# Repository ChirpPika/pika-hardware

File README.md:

# pika-hardware
Hardware design for all Pika models

KiCAD 10

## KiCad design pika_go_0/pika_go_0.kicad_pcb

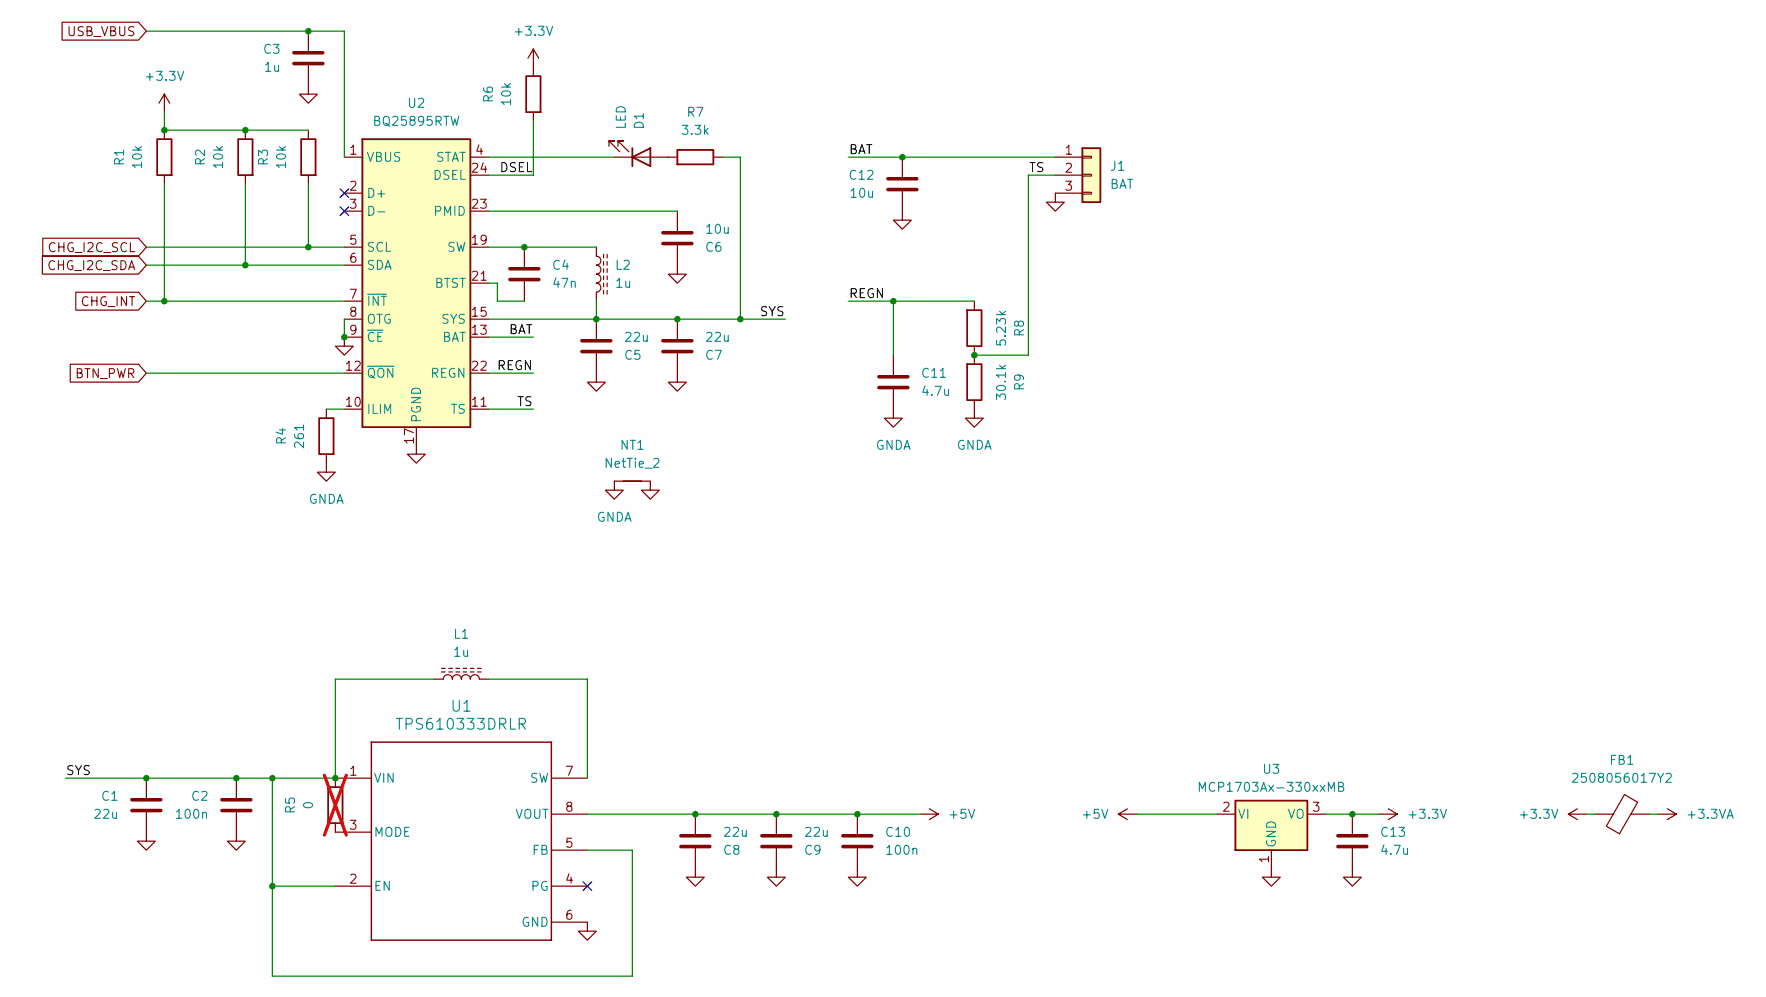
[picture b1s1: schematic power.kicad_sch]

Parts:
C1, C5, C7, C8, C9: 22u; C_0805_2012Metric_Pad1.18x1.45mm_HandSolder
C2, C10: 100n; C_0603_1608Metric_Pad1.08x0.95mm_HandSolder
C3: 1u; C_0603_1608Metric_Pad1.08x0.95mm_HandSolder
C4: 47n; C_0603_1608Metric_Pad1.08x0.95mm_HandSolder
C6, C12: 10u; C_0603_1608Metric_Pad1.08x0.95mm_HandSolder
C11, C13: 4.7u; C_0603_1608Metric_Pad1.08x0.95mm_HandSolder
D1: LED; LED_0603_1608Metric_Pad1.05x0.95mm_HandSolder
FB1: 2508056017Y2; L_0805_2012Metric_Pad1.05x1.20mm_HandSolder
J1: BAT; JST_PH_S3B-PH-K_1x03_P2.00mm_Horizontal
L1, L2: 1u; L_ABRACON_AMELH4018S
NT1: NetTie_2; NetTie-2_SMD_Pad0.5mm
R1, R2, R3, R6: 10k; R_0603_1608Metric_Pad0.98x0.95mm_HandSolder
R4: 261; R_0603_1608Metric_Pad0.98x0.95mm_HandSolder; Tolerance 1%
R5: 0; R_0603_1608Metric_Pad0.98x0.95mm_HandSolder; not fitted
R7: 3.3k; R_0603_1608Metric_Pad0.98x0.95mm_HandSolder
R8: 5.23k; R_0603_1608Metric_Pad0.98x0.95mm_HandSolder; Tolerance 1%
R9: 30.1k; R_0603_1608Metric_Pad0.98x0.95mm_HandSolder; Tolerance 1%
U1: TPS610333DRLR; SOT-583-8
U2: BQ25895RTW; Texas_RTW_WQFN-24-1EP_4x4mm_P0.5mm_EP2.7x2.7mm_ThermalVias
U3: MCP1703Ax-330xxMB; SOT-89-3

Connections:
+3.3V: C13.1, FB1.1, R1.1, R2.1, R3.1, R6.1, U3.3 (VO); also elsewhere on the board
+3.3VA: FB1.2; also elsewhere on the board
+5V: C8.2, C9.2, C10.1, U1.8 (VOUT), U3.2 (VI); also elsewhere on the board
/Power/BAT: C12.1, J1.1, U2.13 (BAT), U2.14 (BAT)
/Power/DSEL: R6.2, U2.24 (DSEL)
/Power/REGN: C11.1, R8.2, U2.22 (REGN)
/Power/SYS: C1.1, C2.1, C5.2, C7.2, L1.1, L2.2, R5.1, R7.1, U1.1 (VIN), U1.2 (EN), U1.5 (FB), U2.15 (SYS), U2.16 (SYS)
/Power/TS: J1.2, R8.1, R9.2, U2.11 (TS)
BTN_PWR: U2.12 (~QON); also elsewhere on the board
CHG_I2C_SCL: R3.2, U2.5 (SCL); also elsewhere on the board
CHG_I2C_SDA: R2.2, U2.6 (SDA); also elsewhere on the board
CHG_INT: R1.2, U2.7 (~INT); also elsewhere on the board
GND: C1.2, C2.2, C3.2, C5.1, C6.1, C7.1, C8.1, C9.1, C10.2, C12.2, C13.2, J1.3, NT1.2, U1.6 (GND), U2.8 (OTG), U2.9 (~CE), U2.17 (PGND), U2.18 (PGND), U2.25 (PGND), U3.1 (GND); also elsewhere on the board
GNDA: C11.2, NT1.1, R4.2, R9.1
unnamed: C4.1, L2.1, U2.19 (SW), U2.20 (SW)
unnamed: D1.2 (A), R7.2
unnamed: D1.1 (K), U2.4 (STAT)
unnamed: R5.2, U1.3 (MODE)
unnamed: L1.2, U1.7 (SW)
unnamed: C4.2, U2.21 (BTST)
unnamed: R4.1, U2.10 (ILIM)
unnamed: C6.2, U2.23 (PMID)
USB_VBUS: C3.1, U2.1 (VBUS); also elsewhere on the board

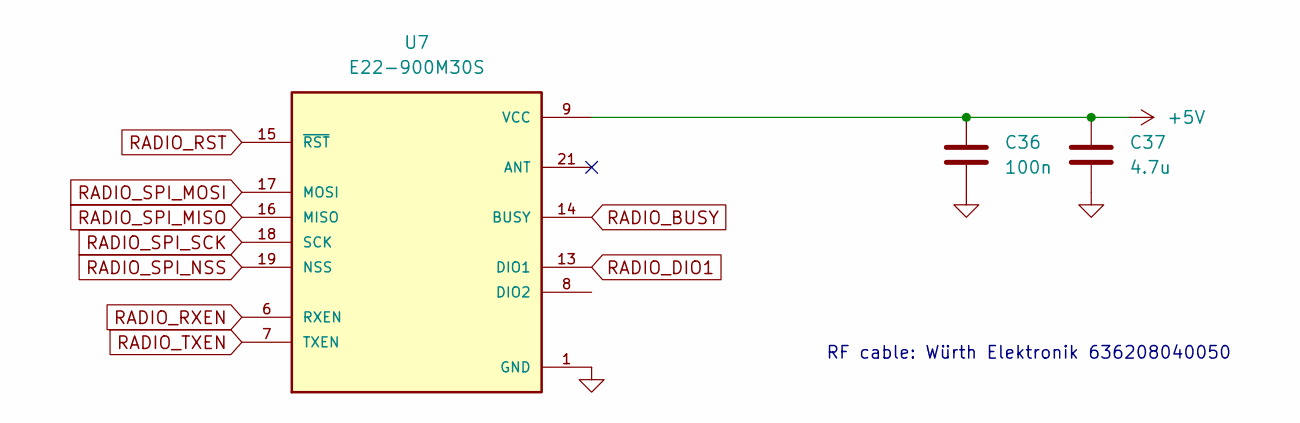
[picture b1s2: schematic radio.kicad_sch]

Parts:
C36: 100n; C_0603_1608Metric_Pad1.08x0.95mm_HandSolder
C37: 4.7u; C_0603_1608Metric_Pad1.08x0.95mm_HandSolder
U7: E22-900M30S; XCVR_E22-900M30S; PARTREV 1.2

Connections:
+5V: C36.1, C37.1, U7.9 (VCC), U7.10 (VCC); also elsewhere on the board
GND: C36.2, C37.2, U7.1 (GND), U7.2 (GND), U7.3 (GND), U7.4 (GND), U7.5 (GND), U7.11 (GND), U7.12 (GND), U7.20 (GND), U7.22 (GND); also elsewhere on the board
RADIO_BUSY: U7.14 (BUSY); also elsewhere on the board
RADIO_DIO1: U7.13 (DIO1); also elsewhere on the board
RADIO_RST: U7.15 (~RST); also elsewhere on the board
RADIO_RXEN: U7.6 (RXEN); also elsewhere on the board
RADIO_SPI_MISO: U7.16 (MISO); also elsewhere on the board
RADIO_SPI_MOSI: U7.17 (MOSI); also elsewhere on the board
RADIO_SPI_NSS: U7.19 (NSS); also elsewhere on the board
RADIO_SPI_SCK: U7.18 (SCK); also elsewhere on the board
RADIO_TXEN: U7.7 (TXEN); also elsewhere on the board

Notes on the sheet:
RF cable: Würth Elektronik 636208040050

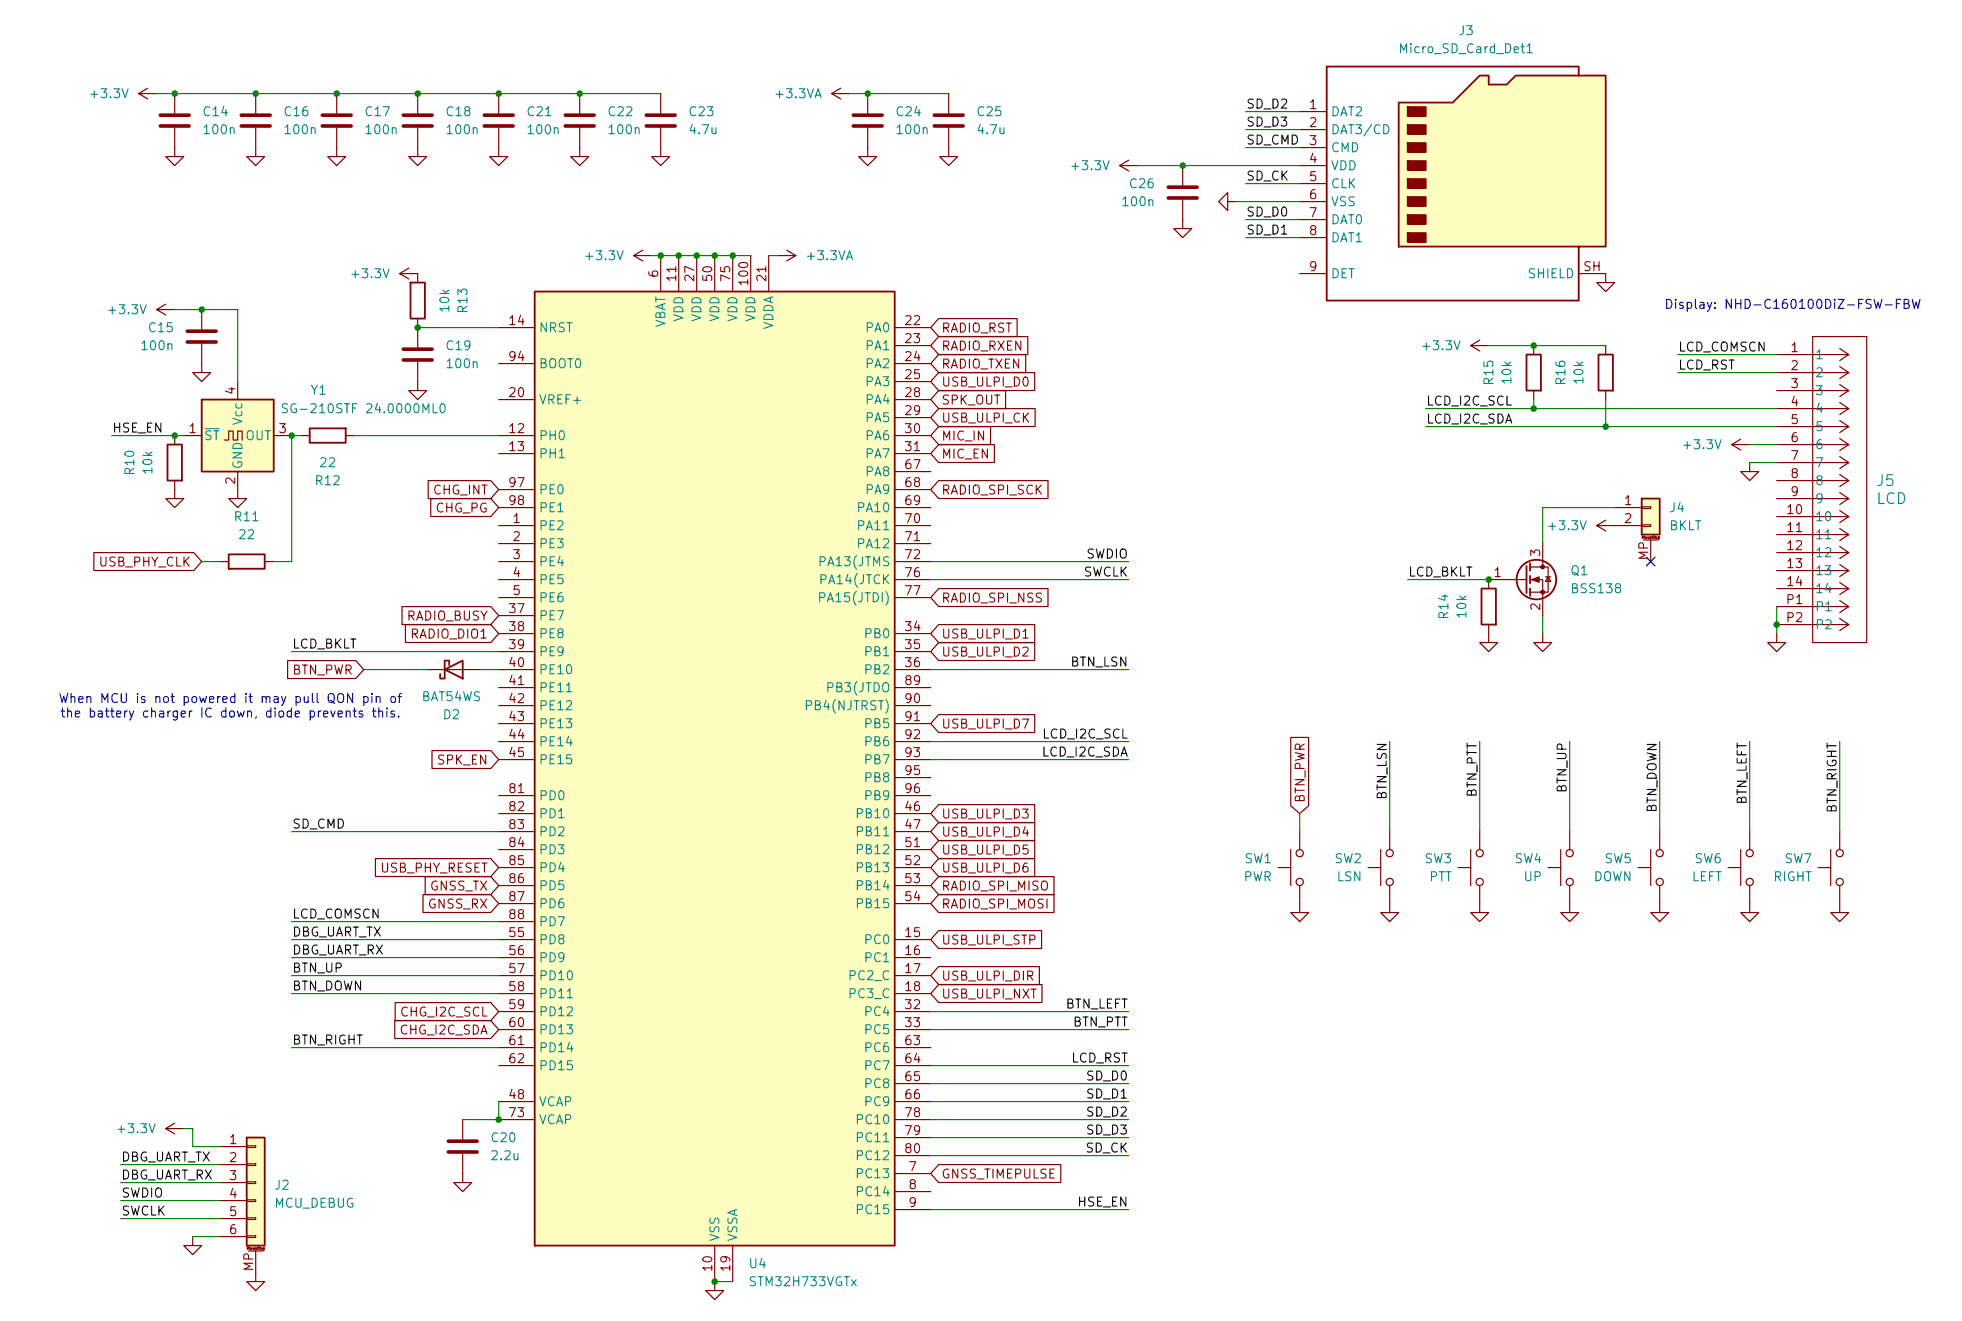
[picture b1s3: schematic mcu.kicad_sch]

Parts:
C14, C15, C16, C17, C18, C19, C21, C22, C24, C26: 100n; C_0603_1608Metric_Pad1.08x0.95mm_HandSolder
C20: 2.2u; C_0603_1608Metric_Pad1.08x0.95mm_HandSolder
C23, C25: 4.7u; C_0603_1608Metric_Pad1.08x0.95mm_HandSolder
D2: BAT54WS; D_SOD-323_HandSoldering
J2: MCU_DEBUG; JST_SH_SM06B-SRSS-TB_1x06-1MP_P1.00mm_Horizontal
J3: Micro_SD_Card_Det1; CUI_MSD-1-A
J4: BKLT; JST_SH_SM02B-SRSS-TB_1x02-1MP_P1.00mm_Horizontal
J5: LCD; 527461471_MOL
Q1: BSS138; SOT-23
R10, R13, R14, R15, R16: 10k; R_0603_1608Metric_Pad0.98x0.95mm_HandSolder
R11, R12: 22; R_0603_1608Metric_Pad0.98x0.95mm_HandSolder
SW1: PWR; SW_SPST_EVQP7C
SW2: LSN; SW_SPST_EVQP7C
SW3: PTT; SW_SPST_EVQP7C
SW4: UP; TE_STSA
SW5: DOWN; TE_STSA
SW6: LEFT; TE_STSA
SW7: RIGHT; TE_STSA
U4: STM32H733VGTx; LQFP-100_14x14mm_P0.5mm
Y1: SG-210STF 24.0000ML0; Oscillator_SMD_SeikoEpson_SG210-4Pin_2.5x2.0mm

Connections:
+3.3V: C14.1, C15.1, C16.1, C17.1, C18.1, C21.1, C22.1, C23.1, C26.1, J2.1, J3.4 (VDD), J4.2, J5.6, R13.2, R15.1, R16.1, U4.6 (VBAT), U4.11 (VDD), U4.27 (VDD), U4.50 (VDD), U4.75 (VDD), U4.100 (VDD), Y1.4 (Vcc); also elsewhere on the board
+3.3VA: C24.1, C25.1, U4.21 (VDDA); also elsewhere on the board
/MCU/BTN_DOWN: SW5.1, U4.58 (PD11)
/MCU/BTN_LEFT: SW6.1, U4.32 (PC4)
/MCU/BTN_LSN: SW2.1, U4.36 (PB2)
/MCU/BTN_PTT: SW3.1, U4.33 (PC5)
/MCU/BTN_RIGHT: SW7.1, U4.61 (PD14)
/MCU/BTN_UP: SW4.1, U4.57 (PD10)
/MCU/DBG_UART_RX: J2.3, U4.56 (PD9)
/MCU/DBG_UART_TX: J2.2, U4.55 (PD8)
/MCU/HSE_EN: R10.1, U4.9 (PC15), Y1.1 (~ST)
/MCU/LCD_BKLT: Q1.1 (G), R14.1, U4.39 (PE9)
/MCU/LCD_COMSCN: J5.1, U4.88 (PD7)
/MCU/LCD_I2C_SCL: J5.4, R15.2, U4.92 (PB6)
/MCU/LCD_I2C_SDA: J5.5, R16.2, U4.93 (PB7)
/MCU/LCD_RST: J5.2, U4.64 (PC7)
/MCU/SD_CK: J3.5 (CLK), U4.80 (PC12)
/MCU/SD_CMD: J3.3 (CMD), U4.83 (PD2)
/MCU/SD_D0: J3.7 (DAT0), U4.65 (PC8)
/MCU/SD_D1: J3.8 (DAT1), U4.66 (PC9)
/MCU/SD_D2: J3.1 (DAT2), U4.78 (PC10)
/MCU/SD_D3: J3.2 (DAT3/CD), U4.79 (PC11)
/MCU/SWCLK: J2.5, U4.76 (PA14(JTCK)
/MCU/SWDIO: J2.4, U4.72 (PA13(JTMS)
BTN_PWR: D2.1 (K), SW1.1; also elsewhere on the board
CHG_I2C_SCL: U4.59 (PD12); also elsewhere on the board
CHG_I2C_SDA: U4.60 (PD13); also elsewhere on the board
CHG_INT: U4.97 (PE0); also elsewhere on the board
CHG_PG: U4.98 (PE1)
GND: C14.2, C15.2, C16.2, C17.2, C18.2, C19.2, C20.2, C21.2, C22.2, C23.2, C24.2, C25.2, C26.2, J2.6, J2.MP (MountPin), J3.6 (VSS), J3.SH (SHIELD), J5.7, J5.P1, J5.P2, Q1.2 (S), R10.2, R14.2, SW1.2, SW2.2, SW3.2, SW4.2, SW5.2, SW6.2, SW7.2, U4.10 (VSS), U4.19 (VSSA), U4.26 (VSS), U4.49 (VSS), U4.74 (VSS), U4.99 (VSS), Y1.2 (GND); also elsewhere on the board
GNSS_RX: U4.87 (PD6); also elsewhere on the board
GNSS_TIMEPULSE: U4.7 (PC13); also elsewhere on the board
GNSS_TX: U4.86 (PD5); also elsewhere on the board
MIC_EN: U4.31 (PA7); also elsewhere on the board
MIC_IN: U4.30 (PA6); also elsewhere on the board
unnamed: C20.1, U4.48 (VCAP), U4.73 (VCAP)
unnamed: D2.2 (A), U4.40 (PE10)
unnamed: J4.1, Q1.3 (D)
unnamed: C19.1, R13.1, U4.14 (NRST)
unnamed: R12.2, U4.12 (PH0)
unnamed: R11.1, R12.1, Y1.3 (OUT)
RADIO_BUSY: U4.37 (PE7); also elsewhere on the board
RADIO_DIO1: U4.38 (PE8); also elsewhere on the board
RADIO_RST: U4.22 (PA0); also elsewhere on the board
RADIO_RXEN: U4.23 (PA1); also elsewhere on the board
RADIO_SPI_MISO: U4.53 (PB14); also elsewhere on the board
RADIO_SPI_MOSI: U4.54 (PB15); also elsewhere on the board
RADIO_SPI_NSS: U4.77 (PA15(JTDI)); also elsewhere on the board
RADIO_SPI_SCK: U4.68 (PA9); also elsewhere on the board
RADIO_TXEN: U4.24 (PA2); also elsewhere on the board
SPK_EN: U4.45 (PE15); also elsewhere on the board
SPK_OUT: U4.28 (PA4); also elsewhere on the board
USB_PHY_CLK: R11.2; also elsewhere on the board
USB_PHY_RESET: U4.85 (PD4); also elsewhere on the board
USB_ULPI_CK: U4.29 (PA5); also elsewhere on the board
USB_ULPI_D0: U4.25 (PA3); also elsewhere on the board
USB_ULPI_D1: U4.34 (PB0); also elsewhere on the board
USB_ULPI_D2: U4.35 (PB1); also elsewhere on the board
USB_ULPI_D3: U4.46 (PB10); also elsewhere on the board
USB_ULPI_D4: U4.47 (PB11); also elsewhere on the board
USB_ULPI_D5: U4.51 (PB12); also elsewhere on the board
USB_ULPI_D6: U4.52 (PB13); also elsewhere on the board
USB_ULPI_D7: U4.91 (PB5); also elsewhere on the board
USB_ULPI_DIR: U4.17 (PC2_C); also elsewhere on the board
USB_ULPI_NXT: U4.18 (PC3_C); also elsewhere on the board
USB_ULPI_STP: U4.15 (PC0); also elsewhere on the board

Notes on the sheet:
When MCU is not powered it may pull QON pin of the battery charger IC down, diode prevents this.
Display: NHD-C160100DiZ-FSW-FBW

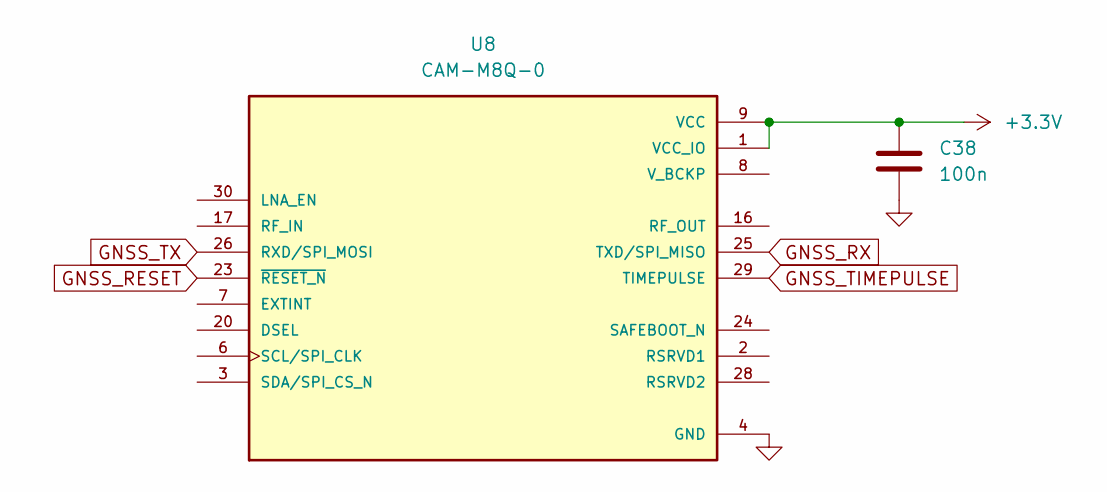
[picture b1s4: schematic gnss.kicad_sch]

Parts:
C38: 100n; C_0603_1608Metric_Pad1.08x0.95mm_HandSolder
U8: CAM-M8Q-0; LCC100P960X1400X210-31N; DigiKey_Part_Number 672-CAM-M8Q-0CT-ND

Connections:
+3.3V: C38.1, U8.1 (VCC_IO), U8.9 (VCC); also elsewhere on the board
GND: C38.2, U8.4 (GND), U8.5 (GND), U8.10 (GND), U8.11 (GND), U8.12 (GND), U8.13 (GND), U8.14 (GND), U8.15 (GND), U8.18 (GND), U8.19 (GND), U8.21 (GND), U8.22 (GND), U8.27 (GND), U8.31 (GND); also elsewhere on the board
GNSS_RESET: U8.23 (~RESET_N)
GNSS_RX: U8.25 (TXD/SPI_MISO); also elsewhere on the board
GNSS_TIMEPULSE: U8.29 (TIMEPULSE); also elsewhere on the board
GNSS_TX: U8.26 (RXD/SPI_MOSI); also elsewhere on the board

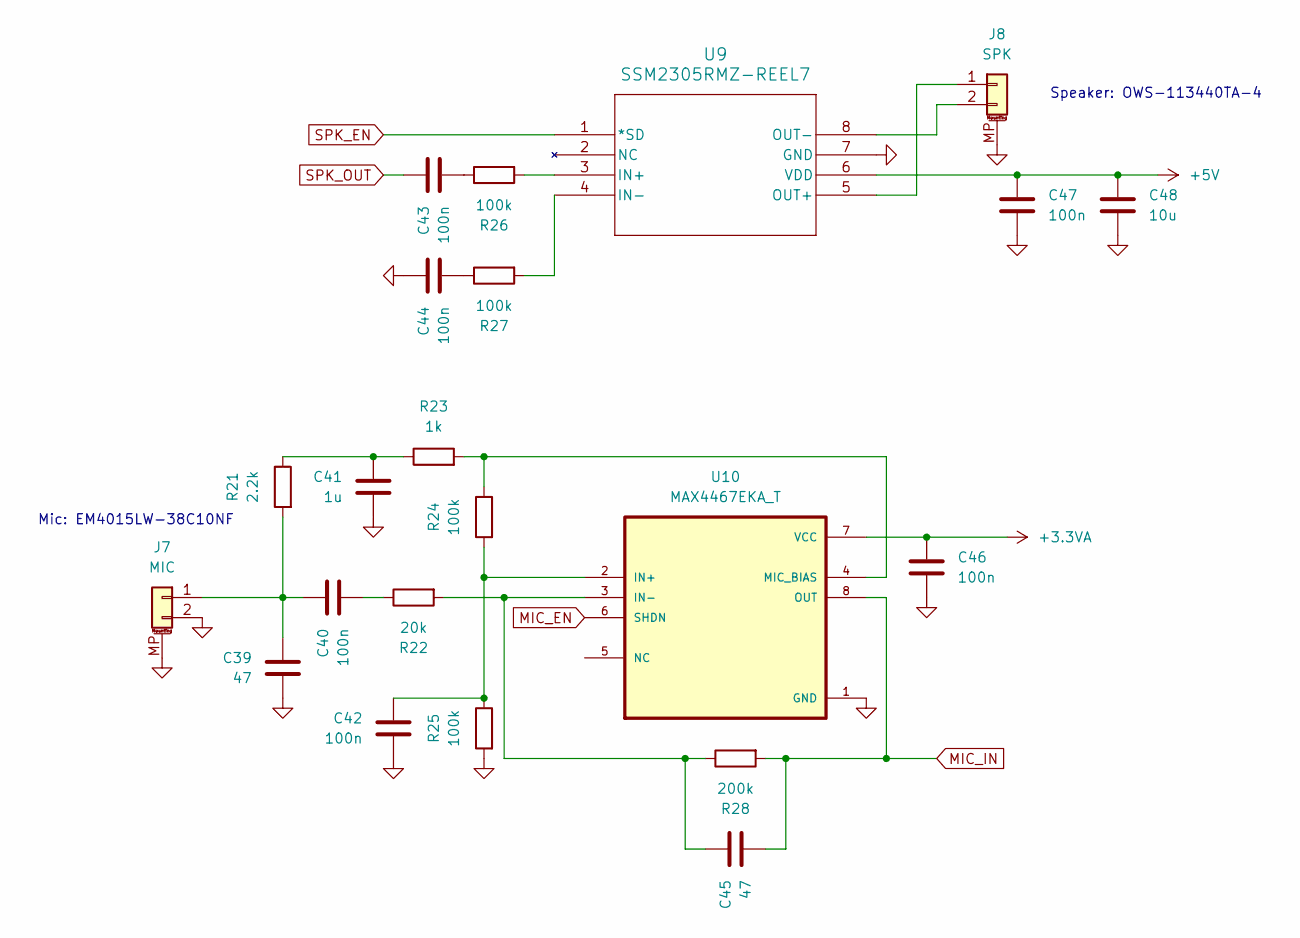
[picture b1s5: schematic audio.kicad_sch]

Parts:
C39, C45: 47; C_0603_1608Metric_Pad1.08x0.95mm_HandSolder
C40, C42, C43, C44, C46, C47: 100n; C_0603_1608Metric_Pad1.08x0.95mm_HandSolder
C41: 1u; C_0603_1608Metric_Pad1.08x0.95mm_HandSolder
C48: 10u; C_0603_1608Metric_Pad1.08x0.95mm_HandSolder
J7: MIC; Molex_PicoBlade_53261-0271_1x02-1MP_P1.25mm_Horizontal
J8: SPK; Molex_PicoBlade_53261-0271_1x02-1MP_P1.25mm_Horizontal
R21: 2.2k; R_0603_1608Metric_Pad0.98x0.95mm_HandSolder
R22: 20k; R_0603_1608Metric_Pad0.98x0.95mm_HandSolder
R23: 1k; R_0603_1608Metric_Pad0.98x0.95mm_HandSolder
R24, R25, R26, R27: 100k; R_0603_1608Metric_Pad0.98x0.95mm_HandSolder
R28: 200k; R_0603_1608Metric_Pad0.98x0.95mm_HandSolder
U9: SSM2305RMZ-REEL7; MSOP-8_3x3mm_P0.65mm
U10: MAX4467EKA_T; SOT-23-8_Handsoldering; DigiKey_Part_Number MAX4467EKA+CT-ND

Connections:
+3.3VA: C46.1, U10.7 (VCC); also elsewhere on the board
+5V: C47.1, C48.1, U9.6 (VDD); also elsewhere on the board
GND: C39.2, C41.2, C42.2, C44.1, C46.2, C47.2, C48.2, J7.2, J7.MP (MountPin), J8.MP (MountPin), R25.2, U9.7 (GND), U10.1 (GND); also elsewhere on the board
MIC_EN: U10.6 (SHDN); also elsewhere on the board
MIC_IN: C45.2, R28.2, U10.8 (OUT); also elsewhere on the board
unnamed: C40.2, R22.1
unnamed: C41.1, R21.1, R23.1
unnamed: C43.2, R26.1
unnamed: C44.2, R27.1
unnamed: C39.1, C40.1, J7.1, R21.2
unnamed: J8.1, U9.5 (OUT+)
unnamed: J8.2, U9.8 (OUT-)
unnamed: R26.2, U9.3 (IN+)
unnamed: R27.2, U9.4 (IN-)
unnamed: C42.1, R24.2, R25.1, U10.2 (IN+)
unnamed: C45.1, R22.2, R28.1, U10.3 (IN-)
unnamed: R23.2, R24.1, U10.4 (MIC_BIAS)
SPK_EN: U9.1 (*SD); also elsewhere on the board
SPK_OUT: C43.1; also elsewhere on the board

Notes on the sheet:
Mic: EM4015LW-38C10NF
Speaker: OWS-113440TA-4

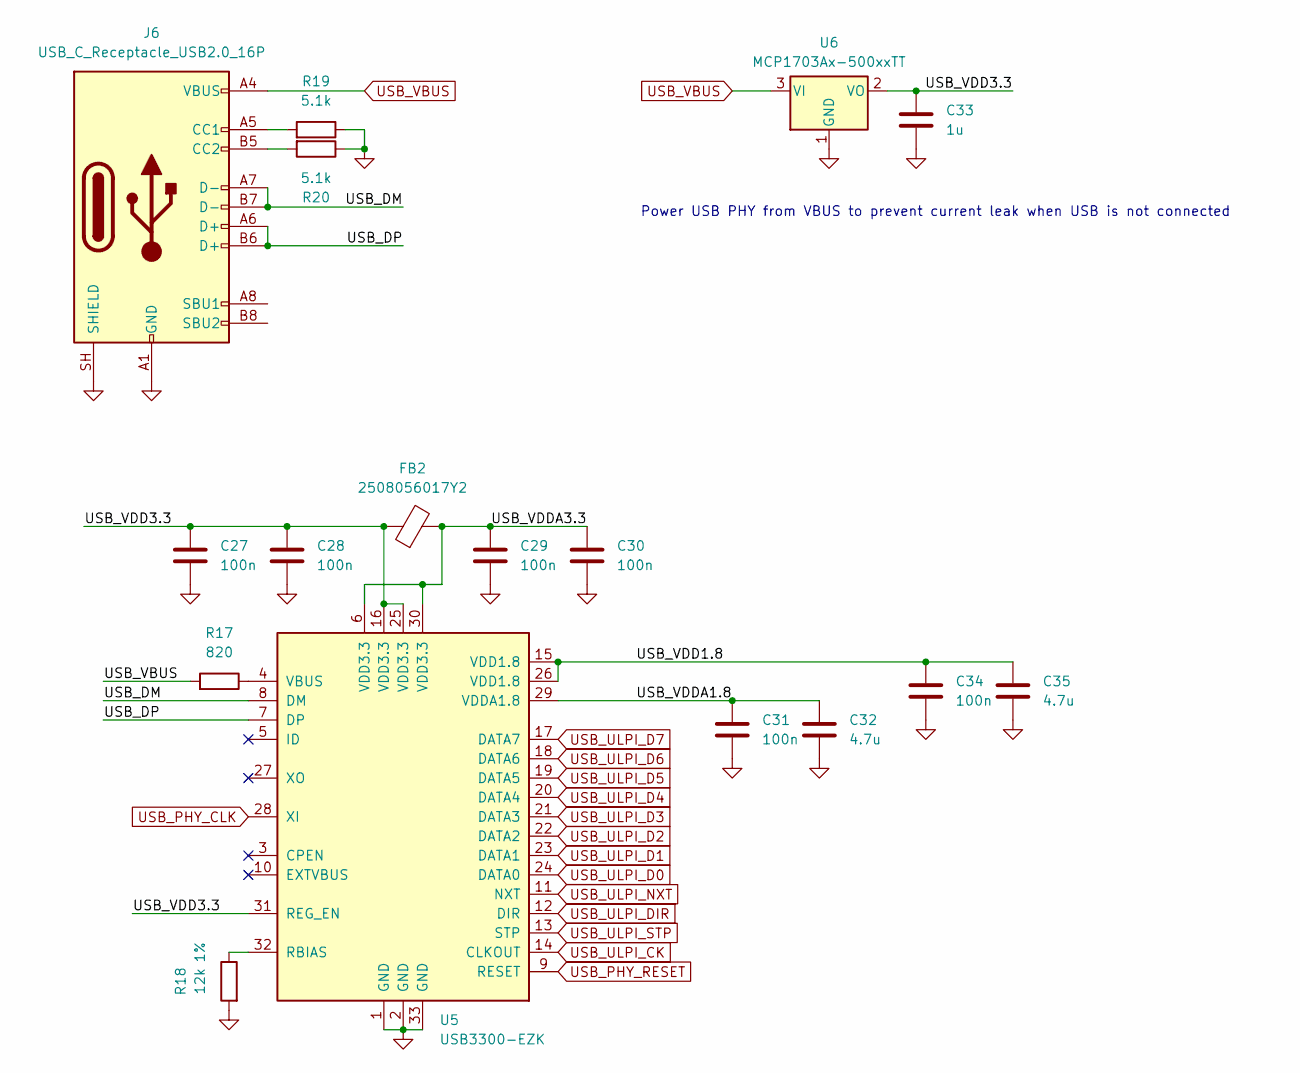
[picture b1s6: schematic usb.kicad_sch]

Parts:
C27, C28, C29, C30, C31, C34: 100n; C_0603_1608Metric_Pad1.08x0.95mm_HandSolder
C32, C35: 4.7u; C_0603_1608Metric_Pad1.08x0.95mm_HandSolder
C33: 1u; C_0603_1608Metric_Pad1.08x0.95mm_HandSolder
FB2: 2508056017Y2; L_0805_2012Metric_Pad1.05x1.20mm_HandSolder
J6: USB_C_Receptacle_USB2.0_16P; AMPHENOL_12402484E512A
R17: 820; R_0603_1608Metric_Pad0.98x0.95mm_HandSolder; Tolerance 1%
R18: 12k; R_0603_1608Metric_Pad0.98x0.95mm_HandSolder; Tolerance 1%
R19, R20: 5.1k; R_0603_1608Metric_Pad0.98x0.95mm_HandSolder
U5: USB3300-EZK; QFN-32-1EP_5x5mm_P0.5mm_EP3.45x3.45mm
U6: MCP1703Ax-500xxTT; SOT-23

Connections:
/USB/USB_DM: J6.A7 (D-), J6.B7 (D-), U5.8 (DM)
/USB/USB_DP: J6.A6 (D+), J6.B6 (D+), U5.7 (DP)
/USB/USB_VDD1.8: C34.1, C35.1, U5.15 (VDD1.8), U5.26 (VDD1.8)
/USB/USB_VDD3.3: C27.1, C28.1, C33.1, FB2.1, U5.16 (VDD3.3), U5.25 (VDD3.3), U5.31 (REG_EN), U6.2 (VO)
/USB/USB_VDDA1.8: C31.1, C32.1, U5.29 (VDDA1.8)
/USB/USB_VDDA3.3: C29.1, C30.1, FB2.2, U5.6 (VDD3.3), U5.30 (VDD3.3)
GND: C27.2, C28.2, C29.2, C30.2, C31.2, C32.2, C33.2, C34.2, C35.2, J6.A1 (GND), J6.A12 (GND), J6.B1 (GND), J6.B12 (GND), J6.SH (SHIELD), R18.2, R19.1, R20.1, U5.1 (GND), U5.2 (GND), U5.33 (GND), U6.1 (GND); also elsewhere on the board
unnamed: J6.A5 (CC1), R19.2
unnamed: J6.B5 (CC2), R20.2
unnamed: R18.1, U5.32 (RBIAS)
unnamed: R17.1, U5.4 (VBUS)
USB_PHY_CLK: U5.28 (XI); also elsewhere on the board
USB_PHY_RESET: U5.9 (RESET); also elsewhere on the board
USB_ULPI_CK: U5.14 (CLKOUT); also elsewhere on the board
USB_ULPI_D0: U5.24 (DATA0); also elsewhere on the board
USB_ULPI_D1: U5.23 (DATA1); also elsewhere on the board
USB_ULPI_D2: U5.22 (DATA2); also elsewhere on the board
USB_ULPI_D3: U5.21 (DATA3); also elsewhere on the board
USB_ULPI_D4: U5.20 (DATA4); also elsewhere on the board
USB_ULPI_D5: U5.19 (DATA5); also elsewhere on the board
USB_ULPI_D6: U5.18 (DATA6); also elsewhere on the board
USB_ULPI_D7: U5.17 (DATA7); also elsewhere on the board
USB_ULPI_DIR: U5.12 (DIR); also elsewhere on the board
USB_ULPI_NXT: U5.11 (NXT); also elsewhere on the board
USB_ULPI_STP: U5.13 (STP); also elsewhere on the board
USB_VBUS: J6.A4 (VBUS), J6.A9 (VBUS), J6.B4 (VBUS), J6.B9 (VBUS), R17.2, U6.3 (VI); also elsewhere on the board

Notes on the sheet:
Power USB PHY from VBUS to prevent current leak when USB is not connected

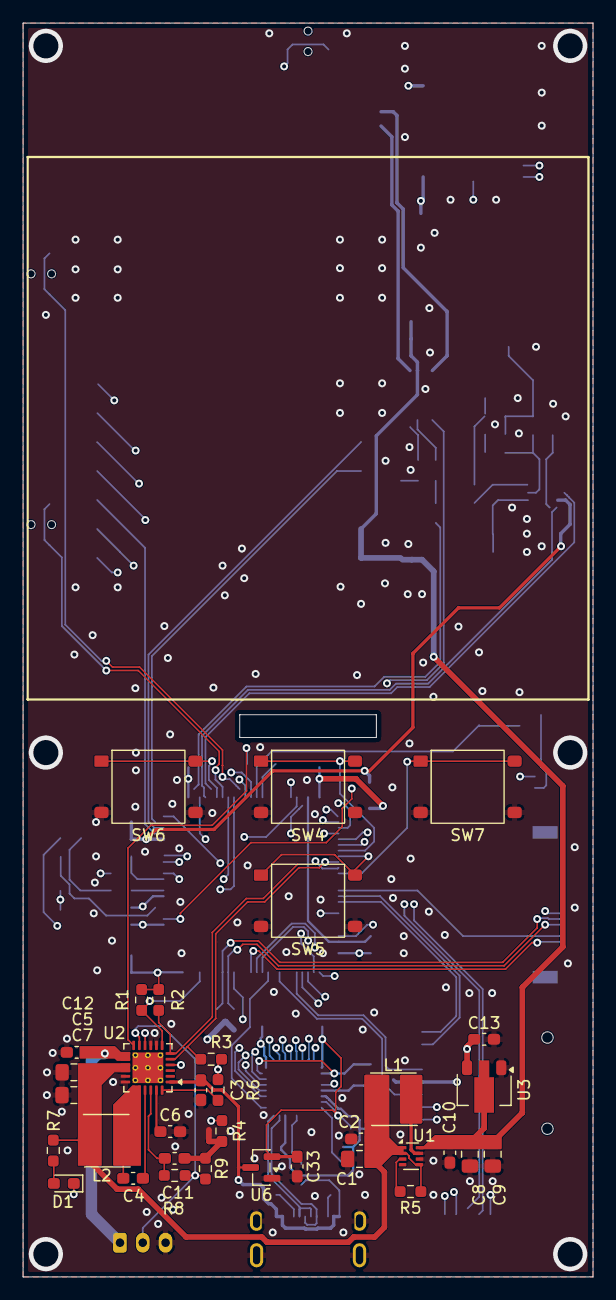
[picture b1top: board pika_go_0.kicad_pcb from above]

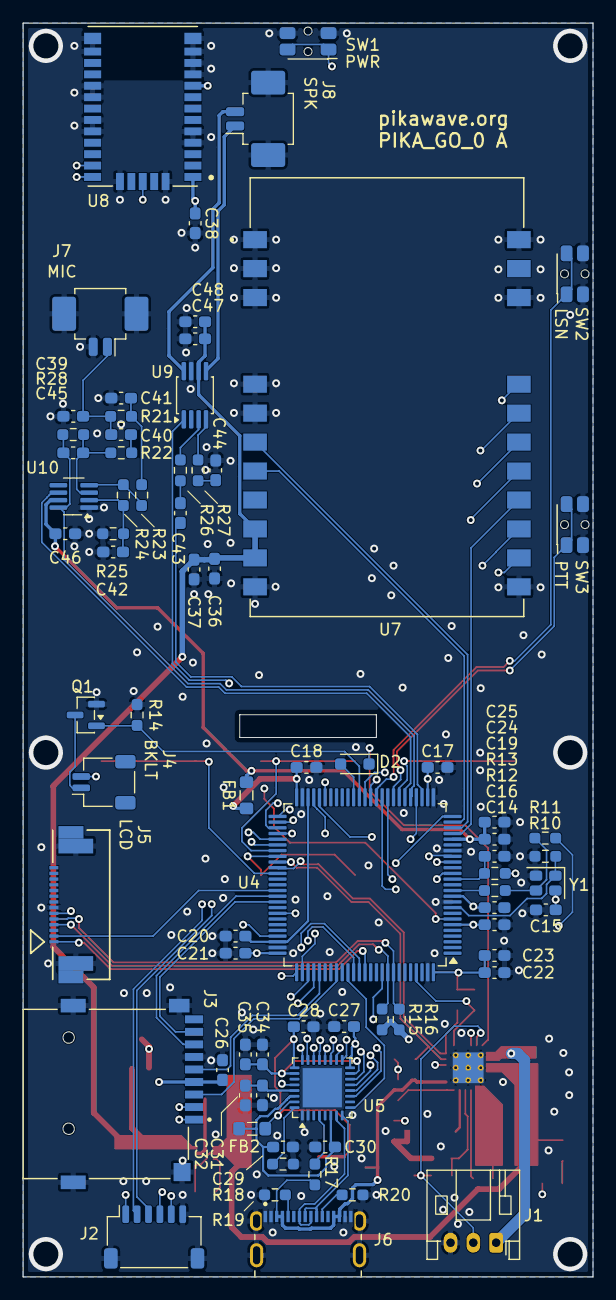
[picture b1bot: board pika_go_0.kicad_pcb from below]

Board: 4 copper layers, 50.0 x 110.0 mm, 110 parts (75 on the bottom side), 103 nets.

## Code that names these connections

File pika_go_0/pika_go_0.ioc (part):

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Mcu.Name=STM32H733VGTx
Mcu.Package=LQFP100
Mcu.UserName=STM32H733VGTx
PA0.Mode=WakeUp1
PA0.Signal=PWR_WKUP1
PA13(JTMS/SWDIO).Mode=Serial_Wire
PA13(JTMS/SWDIO).Signal=DEBUG_JTMS-SWDIO
PA14(JTCK/SWCLK).Mode=Serial_Wire
PA14(JTCK/SWCLK).Signal=DEBUG_JTCK-SWCLK
PA15(JTDI).Mode=NSS_Signal_Hard_Output
PA15(JTDI).Signal=SPI1_NSS
PA2.Mode=Asynchronous
PA2.Signal=USART2_TX
PA3.Mode=Asynchronous
PA3.Signal=USART2_RX
PA4.Signal=COMP_DAC11_group
PA5.Mode=Full_Duplex_Master
PA5.Signal=SPI1_SCK
PA6.Signal=ADCx_INP3
PA7.Mode=Full_Duplex_Master
PA7.Signal=SPI1_MOSI
PB10.Mode=I2C
PB10.Signal=I2C2_SCL
PB11.Mode=I2C
PB11.Signal=I2C2_SDA
PB13.Mode=SD_4_bits_Wide_bus
PB13.Signal=SDMMC1_D0
PB4(NJTRST).Mode=Full_Duplex_Master
PB4(NJTRST).Signal=SPI1_MISO
PB6.Mode=I2C
PB6.Signal=I2C1_SCL
PB7.Mode=I2C
PB7.Signal=I2C1_SDA
PC10.Mode=SD_4_bits_Wide_bus
PC10.Signal=SDMMC1_D2
PC11.Mode=SD_4_bits_Wide_bus
PC11.Signal=SDMMC1_D3
PC12.Mode=SD_4_bits_Wide_bus
PC12.Signal=SDMMC1_CK
PC13.Mode=Timestamp enabled - Input Enabled to TS
PC13.Signal=RTC_TS
PC14-OSC32_IN.Mode=LSE-External-Oscillator
PC14-OSC32_IN.Signal=RCC_OSC32_IN
PC15-OSC32_OUT.Mode=LSE-External-Oscillator
PC15-OSC32_OUT.Signal=RCC_OSC32_OUT
PC9.Mode=SD_4_bits_Wide_bus
PC9.Signal=SDMMC1_D1
PD2.Mode=SD_4_bits_Wide_bus
PD2.Signal=SDMMC1_CMD
PD8.Mode=Asynchronous
PD8.Signal=USART3_TX
PD9.Mode=Asynchronous
PD9.Signal=USART3_RX
PH0-OSC_IN.Mode=HSE-External-Clock-Source
PH0-OSC_IN.Signal=RCC_OSC_IN
RCC.HSE_VALUE=25000000
RCC.SYSCLKFreq_VALUE=550000000
RCC.SYSCLKSource=RCC_SYSCLKSOURCE_PLLCLK
board=custom
